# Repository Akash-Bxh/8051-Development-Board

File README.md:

# Building an 8051 Microcontroller Development Board
Material: KiCAD software, AT895S2, PCB, soldering kit, capacitor, resistor, display, 7-segment, push button, connector, buzzer, Ferric Chloride, Acetone, Fine abrasive sand paper, etc.

An 8051 Development Board is a hardware platform for projects involving the 8051 microcontroller. It includes the microcontroller, clock and reset circuits, power supply, I/O and peripheral interfaces (ADC, DAC), and supports various development tools. Users can write programs in assembly or high-level languages, compile them, and load them onto the board using assemblers and debuggers.

## Steps to make an 8051 Development Board:
* Design the Circuit: Use PCB design software like KiCAD to design the circuit and choose appropriate footprints for each component. Generate the Gerber files for the design.
* Print the Circuit on Raw PCB: Use the screen printing method to transfer the circuit design onto the raw PCB. Apply ink through a stencil and let it dry near warm air for 20-25 minutes.
* Etching Process: Submerge the PCB in ferric chloride solution to remove unwanted copper. After 10-15 minutes, clean the PCB with acetone to remove excess ink.
* Drilling: Drill holes in the PCB where electronic components will be mounted.
* Footprint Placement: Attach the printed component layout on the non-copper side to guide component placement.
* Soldering Components: Insert components on the PCB and solder them securely to the copper side.

## Applications and Uses of this 8051 Development Board
* Microcontroller Programming: It allows users to load and test programs written for the 8051 microcontroller, typically in assembly or C, through an assembler and debugger.
* Hardware Testing and Development: The board provides an environment for testing I/O ports and peripheral interfaces (ADC, DAC) connected to the 8051 microcontroller. It’s used for controlling devices or reading sensor data.
* Circuit Prototyping: The board is used for prototyping embedded system designs before transferring to a final PCB design for production.
* Peripheral Interfacing: You can connect and control components like sensors, displays, and actuators, making it suitable for hardware projects and experiments.
* Learning Platform: Ideal for education in embedded systems, giving students and developers hands-on experience with 8051 microcontrollers.

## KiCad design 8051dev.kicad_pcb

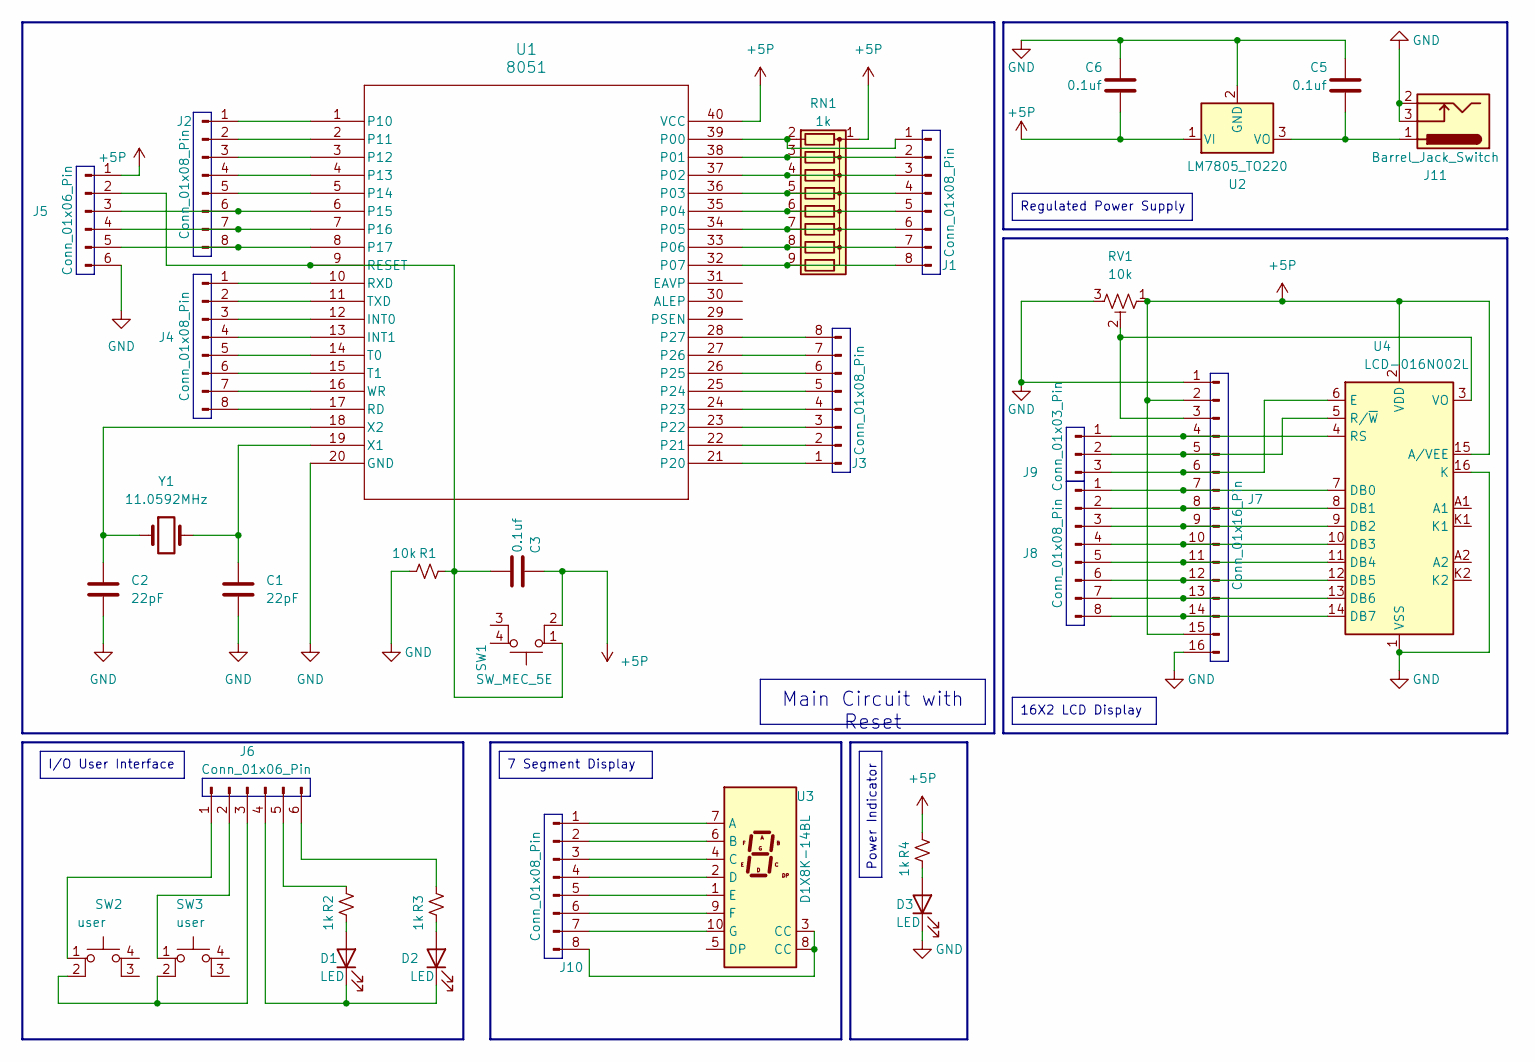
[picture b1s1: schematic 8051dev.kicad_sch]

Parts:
C1, C2: 22pF; C_Disc_D3.8mm_W2.6mm_P2.50mm
C3, C5, C6: 0.1uf; C_Disc_D3.8mm_W2.6mm_P2.50mm
D1, D2, D3: LED; LED_D5.0mm_Clear
J1, J2, J3, J4, J8, J10: Conn_01x08_Pin; PinHeader_1x08_P2.54mm_Vertical
J5, J6: Conn_01x06_Pin; PinHeader_1x06_P2.54mm_Vertical
J7: Conn_01x16_Pin; PinHeader_1x16_P2.54mm_Vertical
J9: Conn_01x03_Pin; PinHeader_1x03_P2.54mm_Vertical
J11: Barrel_Jack_Switch; BarrelJack_Horizontal
R1: 10k; R_Axial_DIN0207_L6.3mm_D2.5mm_P10.16mm_Horizontal
R2, R3: 1k; R_Axial_DIN0204_L3.6mm_D1.6mm_P2.54mm_Vertical
R4: 1k; R_Axial_DIN0207_L6.3mm_D2.5mm_P10.16mm_Horizontal
RN1: 1k; R_Array_SIP9
RV1: 10k; Potentiometer_ACP_CA6-H2,5_Horizontal
SW1: SW_MEC_5E; SW_PUSH_6mm_H4.3mm
SW2, SW3: user; SW_PUSH_6mm_H4.3mm
U1: 8051; DIP-40_W15.24mm
U2: LM7805_TO220; TO-220-3_Vertical
U3: D1X8K-14BL; 7SegmentLED_LTS6760_LTS6780
U4: LCD-016N002L
Y1: 11.0592MHz; Crystal_HC18-U_Vertical

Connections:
+5P: C3.1, C6.2, J5.1, J7.2, J7.15, R4.1, RN1.1 (common), RV1.1, SW1.2, U1.40 (VCC), U2.1 (VI), U4.2 (VDD), U4.15 (A/VEE); also elsewhere on the board
GND: C1.2, C2.1, C5.1, C6.1, D3.1 (K), J5.6, J7.1, J7.16, J11.2, J11.3, R1.2, RV1.3, U1.20 (GND), U2.2 (GND), U4.1 (VSS), U4.16 (K); also elsewhere on the board
unnamed: D1.2 (A), R2.2
unnamed: D1.1 (K), D2.1 (K), J6.4
unnamed: D2.2 (A), R3.2
unnamed: D3.2 (A), R4.2
unnamed: J1.1, RN1.2 (R1), U1.39 (P00)
unnamed: J1.2, RN1.3 (R2), U1.38 (P01)
unnamed: J1.3, RN1.4 (R3), U1.37 (P02)
unnamed: J1.4, RN1.5 (R4), U1.36 (P03)
unnamed: J1.5, RN1.6 (R5), U1.35 (P04)
unnamed: J1.6, RN1.7 (R6), U1.34 (P05)
unnamed: J1.7, RN1.8 (R7), U1.33 (P06)
unnamed: J1.8, RN1.9 (R8), U1.32 (P07)
unnamed: J2.1, U1.1 (P10)
unnamed: J2.2, U1.2 (P11)
unnamed: J2.3, U1.3 (P12)
unnamed: J2.4, U1.4 (P13)
unnamed: J2.5, U1.5 (P14)
unnamed: J2.6, J5.3, U1.6 (P15)
unnamed: J2.7, J5.4, U1.7 (P16)
unnamed: J2.8, J5.5, U1.8 (P17)
unnamed: J3.1, U1.21 (P20)
unnamed: J3.2, U1.22 (P21)
unnamed: J3.3, U1.23 (P22)
unnamed: J3.4, U1.24 (P23)
unnamed: J3.5, U1.25 (P24)
unnamed: J3.6, U1.26 (P25)
unnamed: J3.7, U1.27 (P26)
unnamed: J3.8, U1.28 (P27)
unnamed: J4.1, U1.10 (RXD)
unnamed: J4.2, U1.11 (TXD)
unnamed: J4.3, U1.12 (INT0)
unnamed: J4.4, U1.13 (INT1)
unnamed: J4.5, U1.14 (T0)
unnamed: J4.6, U1.15 (T1)
unnamed: J4.7, U1.16 (WR)
unnamed: J4.8, U1.17 (RD)
unnamed: C3.2, J5.2, R1.1, SW1.1, U1.9 (RESET)
unnamed: J6.1, SW2.1
unnamed: J6.2, SW3.1
unnamed: J6.3, SW2.2, SW3.2
unnamed: J6.5, R2.1
unnamed: J6.6, R3.1
unnamed: J7.3, RV1.2, U4.3 (VO)
unnamed: J7.4, J9.1, U4.4 (RS)
unnamed: J7.5, J9.2, U4.5 (R/~W)
unnamed: J7.6, J9.3, U4.6 (E)
unnamed: J7.7, J8.1, U4.7 (DB0)
unnamed: J7.8, J8.2, U4.8 (DB1)
unnamed: J7.9, J8.3, U4.9 (DB2)
unnamed: J7.10, J8.4, U4.10 (DB3)
unnamed: J7.11, J8.5, U4.11 (DB4)
unnamed: J7.12, J8.6, U4.12 (DB5)
unnamed: J7.13, J8.7, U4.13 (DB6)
unnamed: J7.14, J8.8, U4.14 (DB7)
unnamed: J10.1, U3.7 (A)
unnamed: J10.2, U3.6 (B)
unnamed: J10.3, U3.4 (C)
unnamed: J10.4, U3.2 (D)
unnamed: J10.5, U3.1 (E)
unnamed: J10.6, U3.9 (F)
unnamed: J10.7, U3.10 (G)
unnamed: J10.8, U3.3 (CC), U3.8 (CC)
unnamed: C1.1, U1.19 (X1), Y1.2
unnamed: C2.2, U1.18 (X2), Y1.1
unnamed: C5.2, J11.1, U2.3 (VO)

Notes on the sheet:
I/O User Interface
Power Indicator
16X2 LCD Display
Main Circuit with Reset
7 Segment Display
Regulated Power Supply

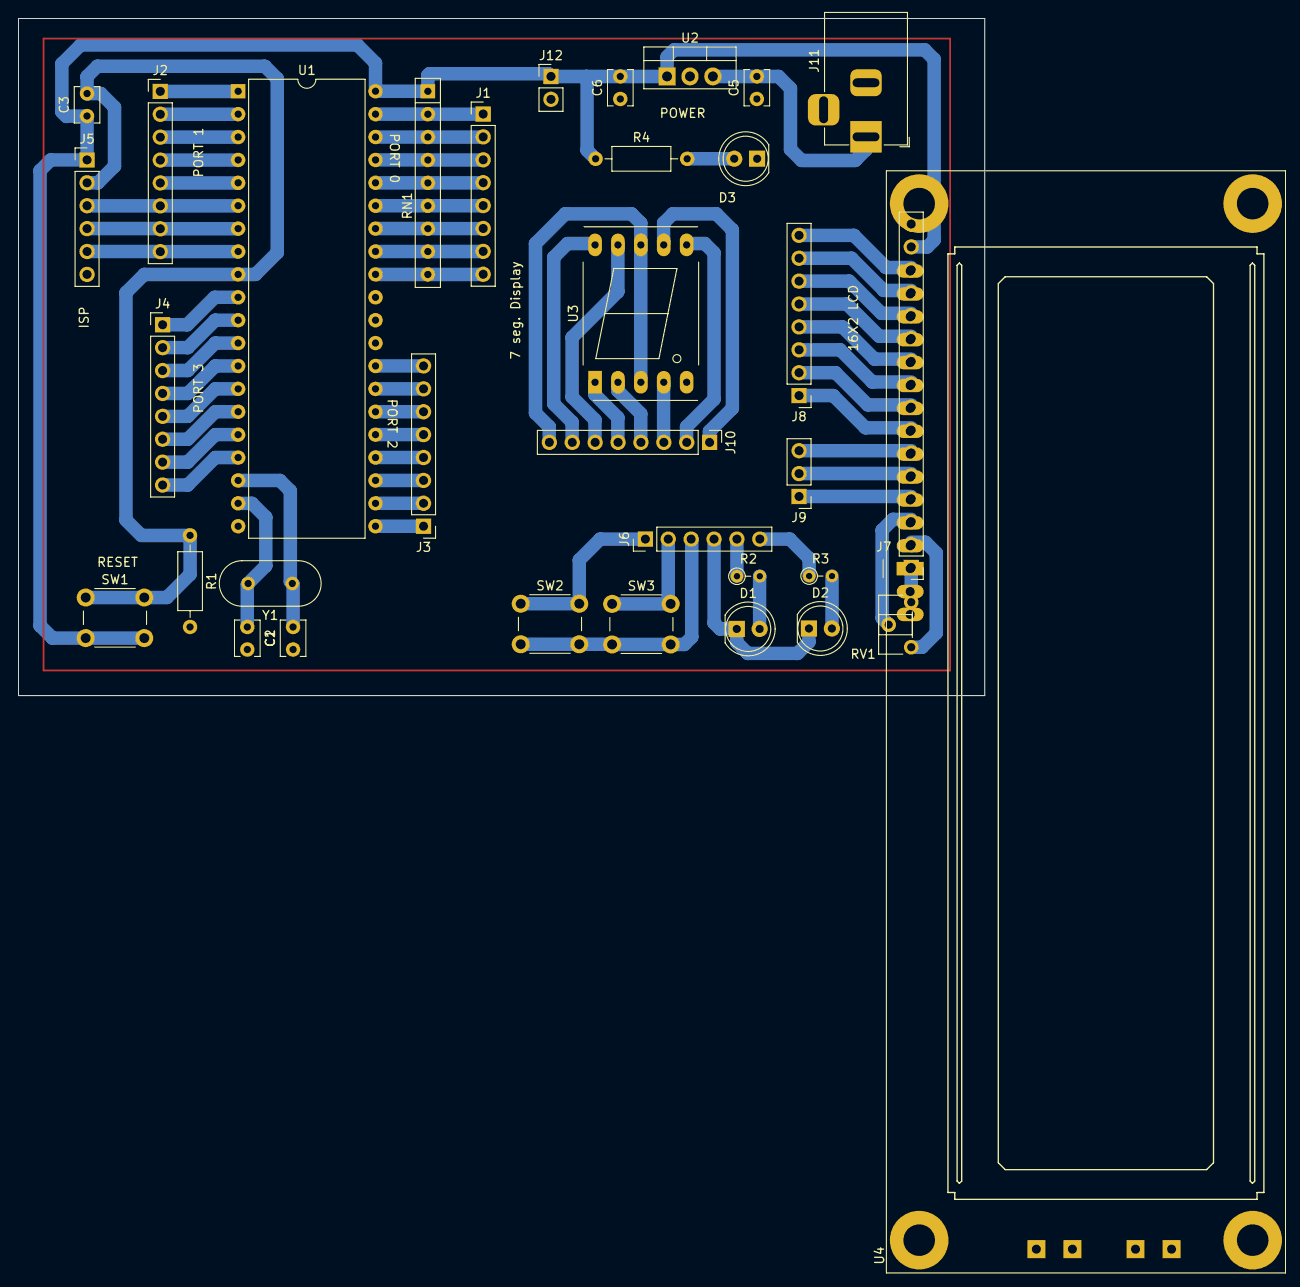
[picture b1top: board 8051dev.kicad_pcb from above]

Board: 2 copper layers, 107.2 x 75.1 mm, 34 parts (0 on the bottom side), 67 nets.

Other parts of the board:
J12: 5v; PinHeader_1x02_P2.54mm_Vertical

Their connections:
+5P: J12.1; also elsewhere on the board
GND: J12.2; also elsewhere on the board
